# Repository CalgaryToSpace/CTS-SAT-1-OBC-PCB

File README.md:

# CTS-SAT-1-OBC-PCB

This is the design repository for the CTS-SAT-1 ("FrontierSat") onboard computer (OBC) PCB.

This OBC is host to an STM32 and several flash chips, and interfaces with all other electrical components on the 3U CubeSat.

## PCB Stackup

This PCB uses the [JLCPCB `JLC04161H-2116A` stackup](https://jlcpcb.com/impedance). It is a 6-layer, impedance-controlled PCB.

## Electrical Wire Comments

It is important to consider the outgassing characteristics of all wires used, so PTFE insulation has been chosen as the standard insulation material. The recommended part number is 5853 BK005, and the maximum recommended current is 1 amp per conductor.

If constructing Space Grade PCBs, use Rogers material as it has low outgassing properties.

## Repository Contents

* OBC PCB
* STM32CubeIDE Pinout/IOC configuration
* Unused early-stage umbilical connection board

## Contributors

* James Chen (contact chen.james2015@gmail.com with any questions)
* Others

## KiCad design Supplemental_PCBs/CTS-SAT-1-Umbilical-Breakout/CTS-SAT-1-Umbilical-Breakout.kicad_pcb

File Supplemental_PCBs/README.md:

# CTS-SAT-1 Supplemental PCBs

In this folder, two PCBs were used to support the development of the CTS-SAT-1 Onboard Computer (OBC).

* `Programming_Connector_Adapter_PCB`: Solder on to an Aliexpress ST-Link, and connect to the OBC with a 6-wide picoblade harness.
* `CTS-SAT-1-Umbilical-Breakout`: Works as a passthrough, and breaks out each pin for easy connection to USB-UART convert. Adds LEDs to each pin, as well as a polyfuse for safe charging.

## Subfolder Organization

* `./Programming_Connector_Adapter_PCB/` depends on `./lib/`.
* `./CTS-SAT-1-Umbilical-Breakout/` is self-contained.

## Render: `CTS-SAT-1-Umbilical-Breakout`

## Render: `Programming_Connector_Adapter_PCB`

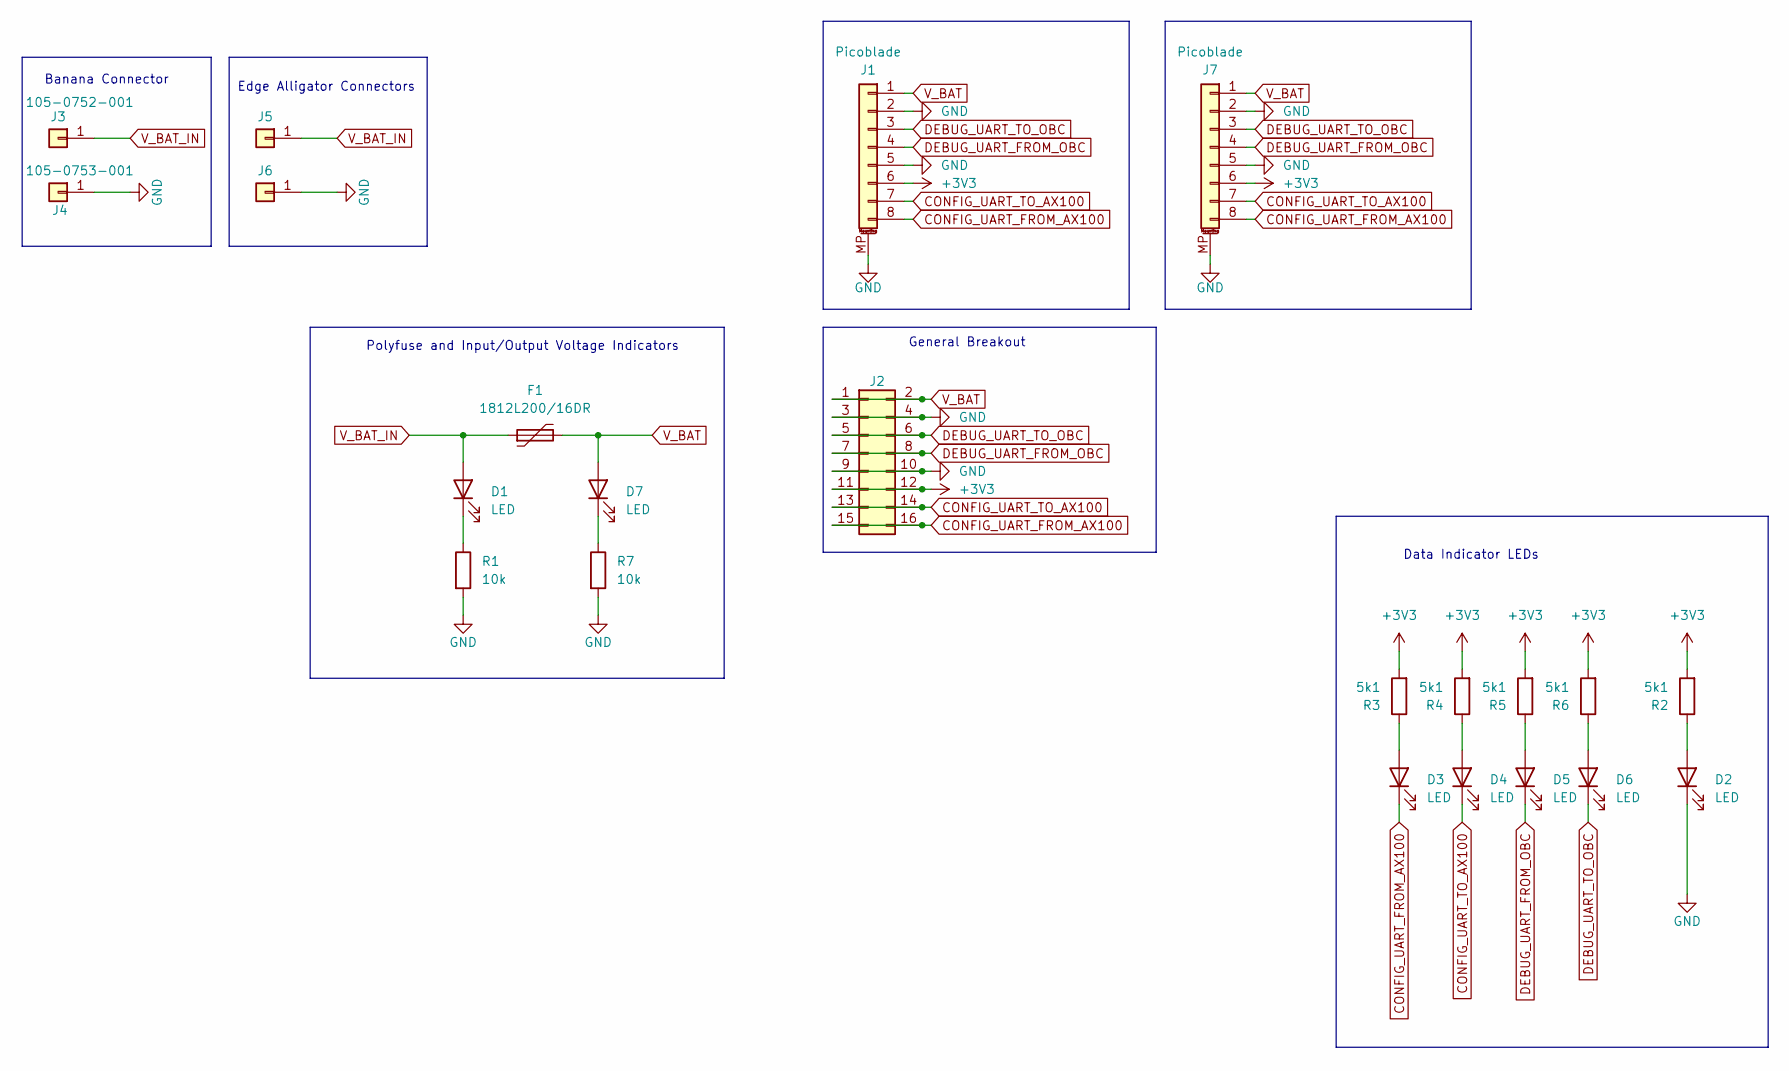
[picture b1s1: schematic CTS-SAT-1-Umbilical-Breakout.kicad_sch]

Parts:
D1, D2, D3, D4, D5, D6, D7: LED; LED_1206_3216Metric_Pad1.42x1.75mm_HandSolder
F1: 1812L200/16DR; Fuse_1812_4532Metric_Pad1.30x3.40mm_HandSolder
J1, J7: Picoblade; Molex_PicoBlade_53261-0871_1x08-1MP_P1.25mm_Horizontal
J2: Conn_02x08_Odd_Even; PinSocket_2x08_P2.54mm_Vertical
J3: 105-0752-001; TestPoint_Bridge_Pitch5.08mm_Drill1.3mm
J4: 105-0753-001; TestPoint_Bridge_Pitch5.08mm_Drill1.3mm
J5, J6: Conn_01x01; EdgeAlligatorConnector
R1, R7: 10k; R_1206_3216Metric_Pad1.30x1.75mm_HandSolder
R2, R3, R4, R5, R6: 5k1; R_1206_3216Metric_Pad1.30x1.75mm_HandSolder

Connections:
+3V3: J1.6, J2.11, J2.12, J7.6, R2.2, R3.2, R4.2, R5.2, R6.2
CONFIG_UART_FROM_AX100: D3.1 (K), J1.8, J2.15, J2.16, J7.8
CONFIG_UART_TO_AX100: D4.1 (K), J1.7, J2.13, J2.14, J7.7
DEBUG_UART_FROM_OBC: D5.1 (K), J1.4, J2.7, J2.8, J7.4
DEBUG_UART_TO_OBC: D6.1 (K), J1.3, J2.5, J2.6, J7.3
GND: D2.1 (K), J1.2, J1.5, J1.MP (MountPin), J2.3, J2.4, J2.9, J2.10, J4.1, J6.1, J7.2, J7.5, J7.MP (MountPin), R1.2, R7.2
unnamed: D1.1 (K), R1.1
unnamed: D2.2 (A), R2.1
unnamed: D3.2 (A), R3.1
unnamed: D4.2 (A), R4.1
unnamed: D5.2 (A), R5.1
unnamed: D6.2 (A), R6.1
unnamed: D7.1 (K), R7.1
V_BAT: D7.2 (A), F1.2, J1.1, J2.1, J2.2, J7.1
V_BAT_IN: D1.2 (A), F1.1, J3.1, J5.1

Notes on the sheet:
Banana Connector
Edge Alligator Connectors
Polyfuse and Input/Output Voltage Indicators
Data Indicator LEDs
General Breakout

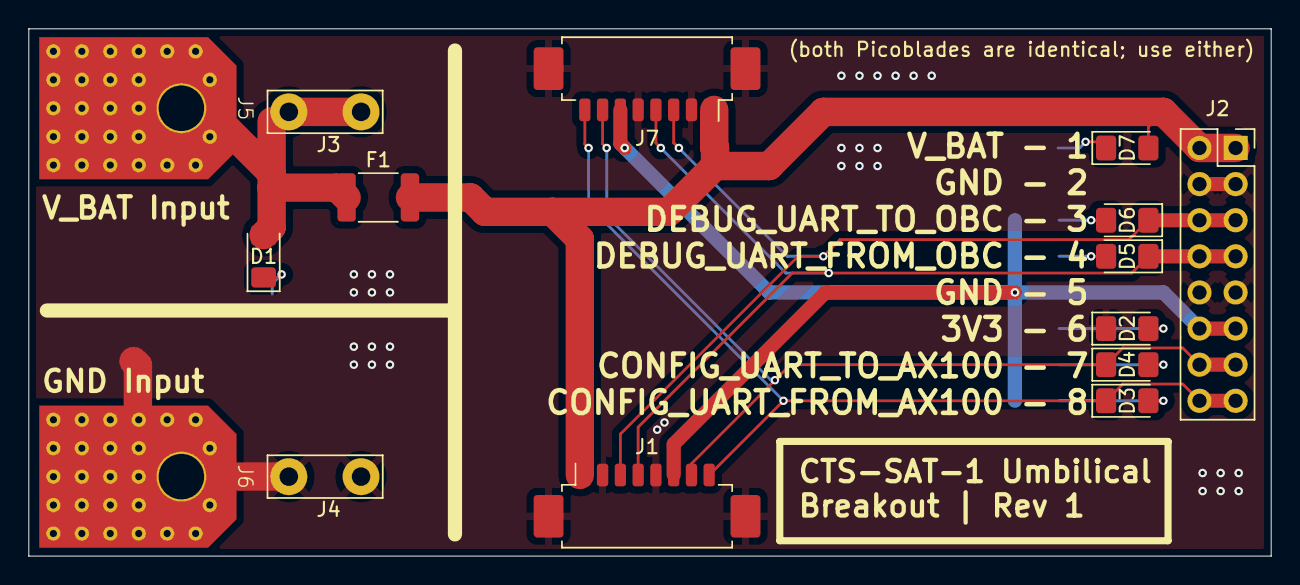
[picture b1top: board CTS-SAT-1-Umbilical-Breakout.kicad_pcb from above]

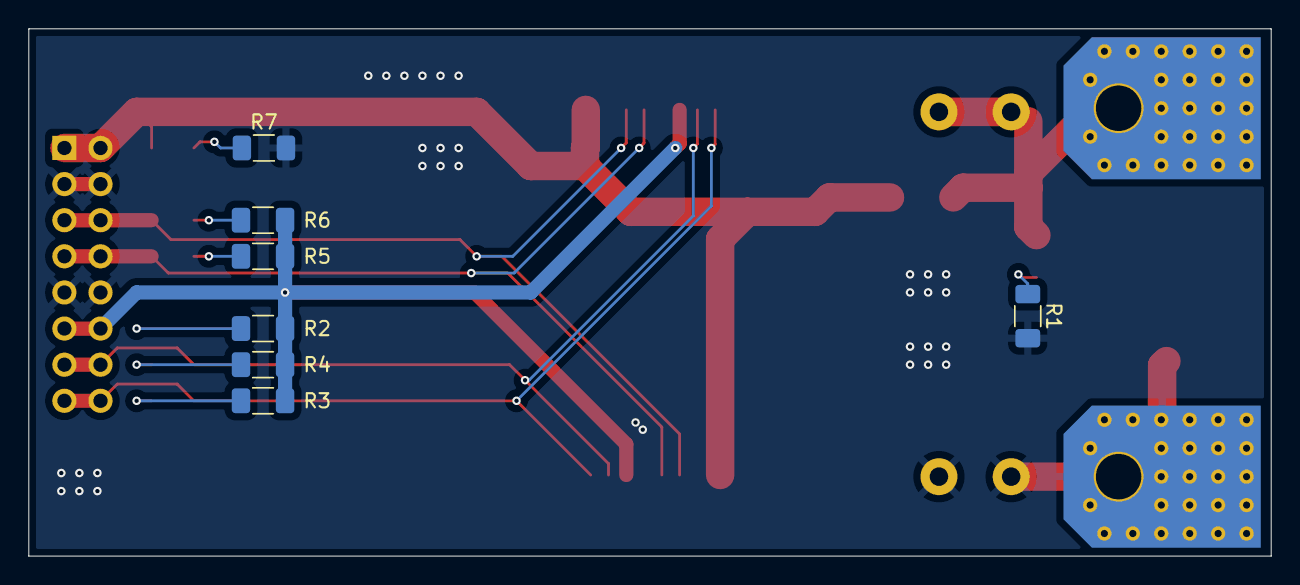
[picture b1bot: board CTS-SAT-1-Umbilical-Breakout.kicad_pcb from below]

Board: 2 copper layers, 87.4 x 37.1 mm, 22 parts (7 on the bottom side), 15 nets.

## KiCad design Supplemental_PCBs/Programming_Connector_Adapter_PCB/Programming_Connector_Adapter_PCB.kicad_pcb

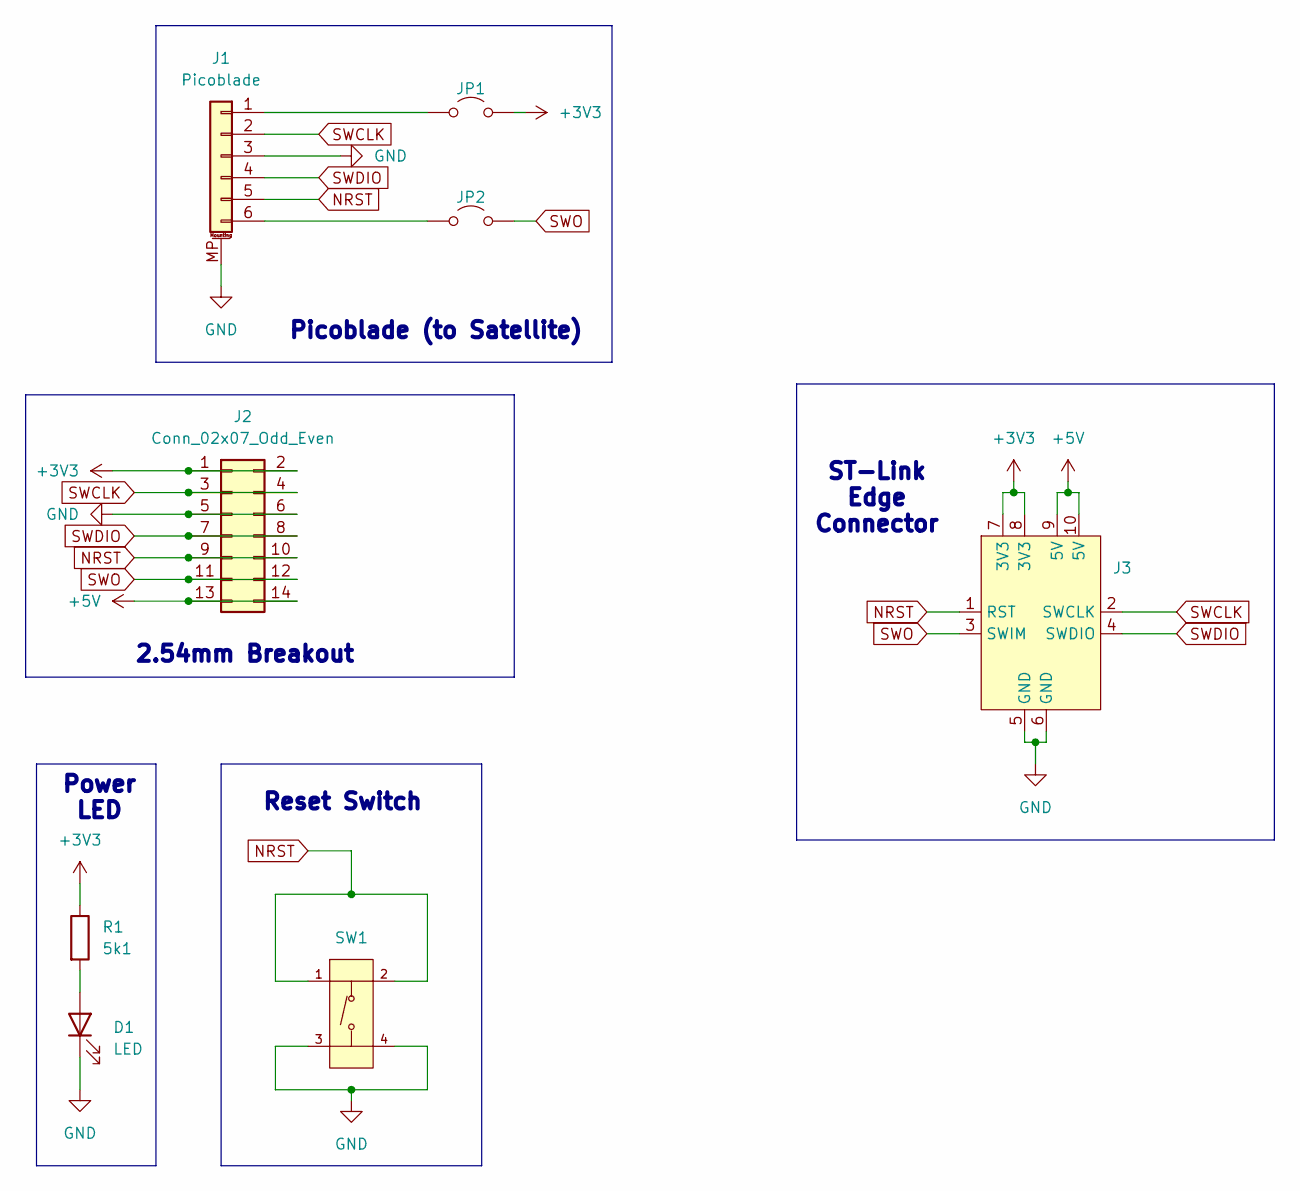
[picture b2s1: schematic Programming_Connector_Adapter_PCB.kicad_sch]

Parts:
D1: LED; LED_0603_1608Metric_Pad1.05x0.95mm_HandSolder
J1: Picoblade; Molex_PicoBlade_53261-0671_1x06-1MP_P1.25mm_Horizontal
J2: Conn_02x07_Odd_Even; PinHeaderSocket_2x07_P2.54mm_Vertical
J3: ST_Link_Edge_Connector
JP1, JP2: Jumper_2_Open; PinHeader_2x01_P2.54mm_Vertical
R1: 5k1; R_0603_1608Metric_Pad0.98x0.95mm_HandSolder
SW1: Tactile_Button,_160gf; SW-SMD_4P-L5.1-W5.1-P3.70-LS6.5-TL-2; Voltage Rating (Dc) 12V; Part TS-1187A-B-A-B; LCSC C318884

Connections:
+3V3: J2.1, J2.2, J3.7 (3V3), J3.8 (3V3), JP1.2 (B), R1.1
+5V: J2.13, J2.14, J3.9 (5V), J3.10 (5V)
GND: D1.1 (K), J1.3, J1.MP (MountPin), J2.5, J2.6, J3.5 (GND), J3.6 (GND), SW1.3 (C), SW1.4 (D)
NRST: J1.5, J2.9, J2.10, J3.1 (RST), SW1.1 (A), SW1.2 (B)
unnamed: D1.2 (A), R1.2
unnamed: J1.1, JP1.1 (A)
unnamed: J1.6, JP2.1 (A)
SWCLK: J1.2, J2.3, J2.4, J3.2 (SWCLK)
SWDIO: J1.4, J2.7, J2.8, J3.4 (SWDIO)
SWO: J2.11, J2.12, J3.3 (SWIM), JP2.2 (B)

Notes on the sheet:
2.54mm Breakout
Power LED
Reset Switch
ST-Link Edge Connector
Picoblade (to Satellite)

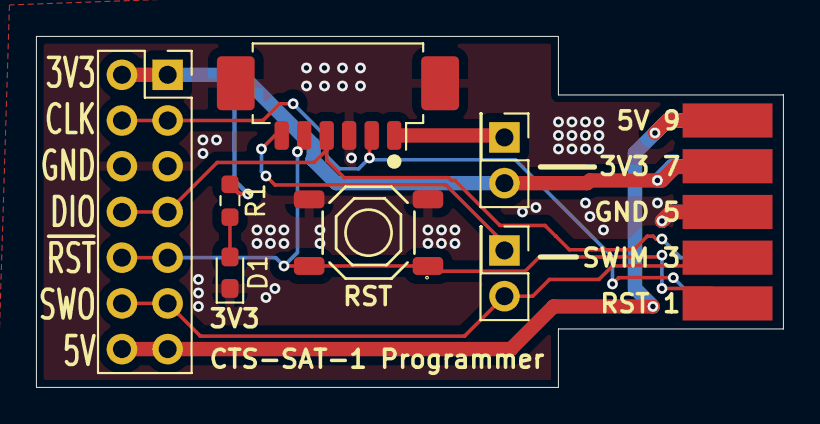
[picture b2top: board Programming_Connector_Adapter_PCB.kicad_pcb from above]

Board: 2 copper layers, 41.5 x 19.5 mm, 8 parts (0 on the bottom side), 10 nets.

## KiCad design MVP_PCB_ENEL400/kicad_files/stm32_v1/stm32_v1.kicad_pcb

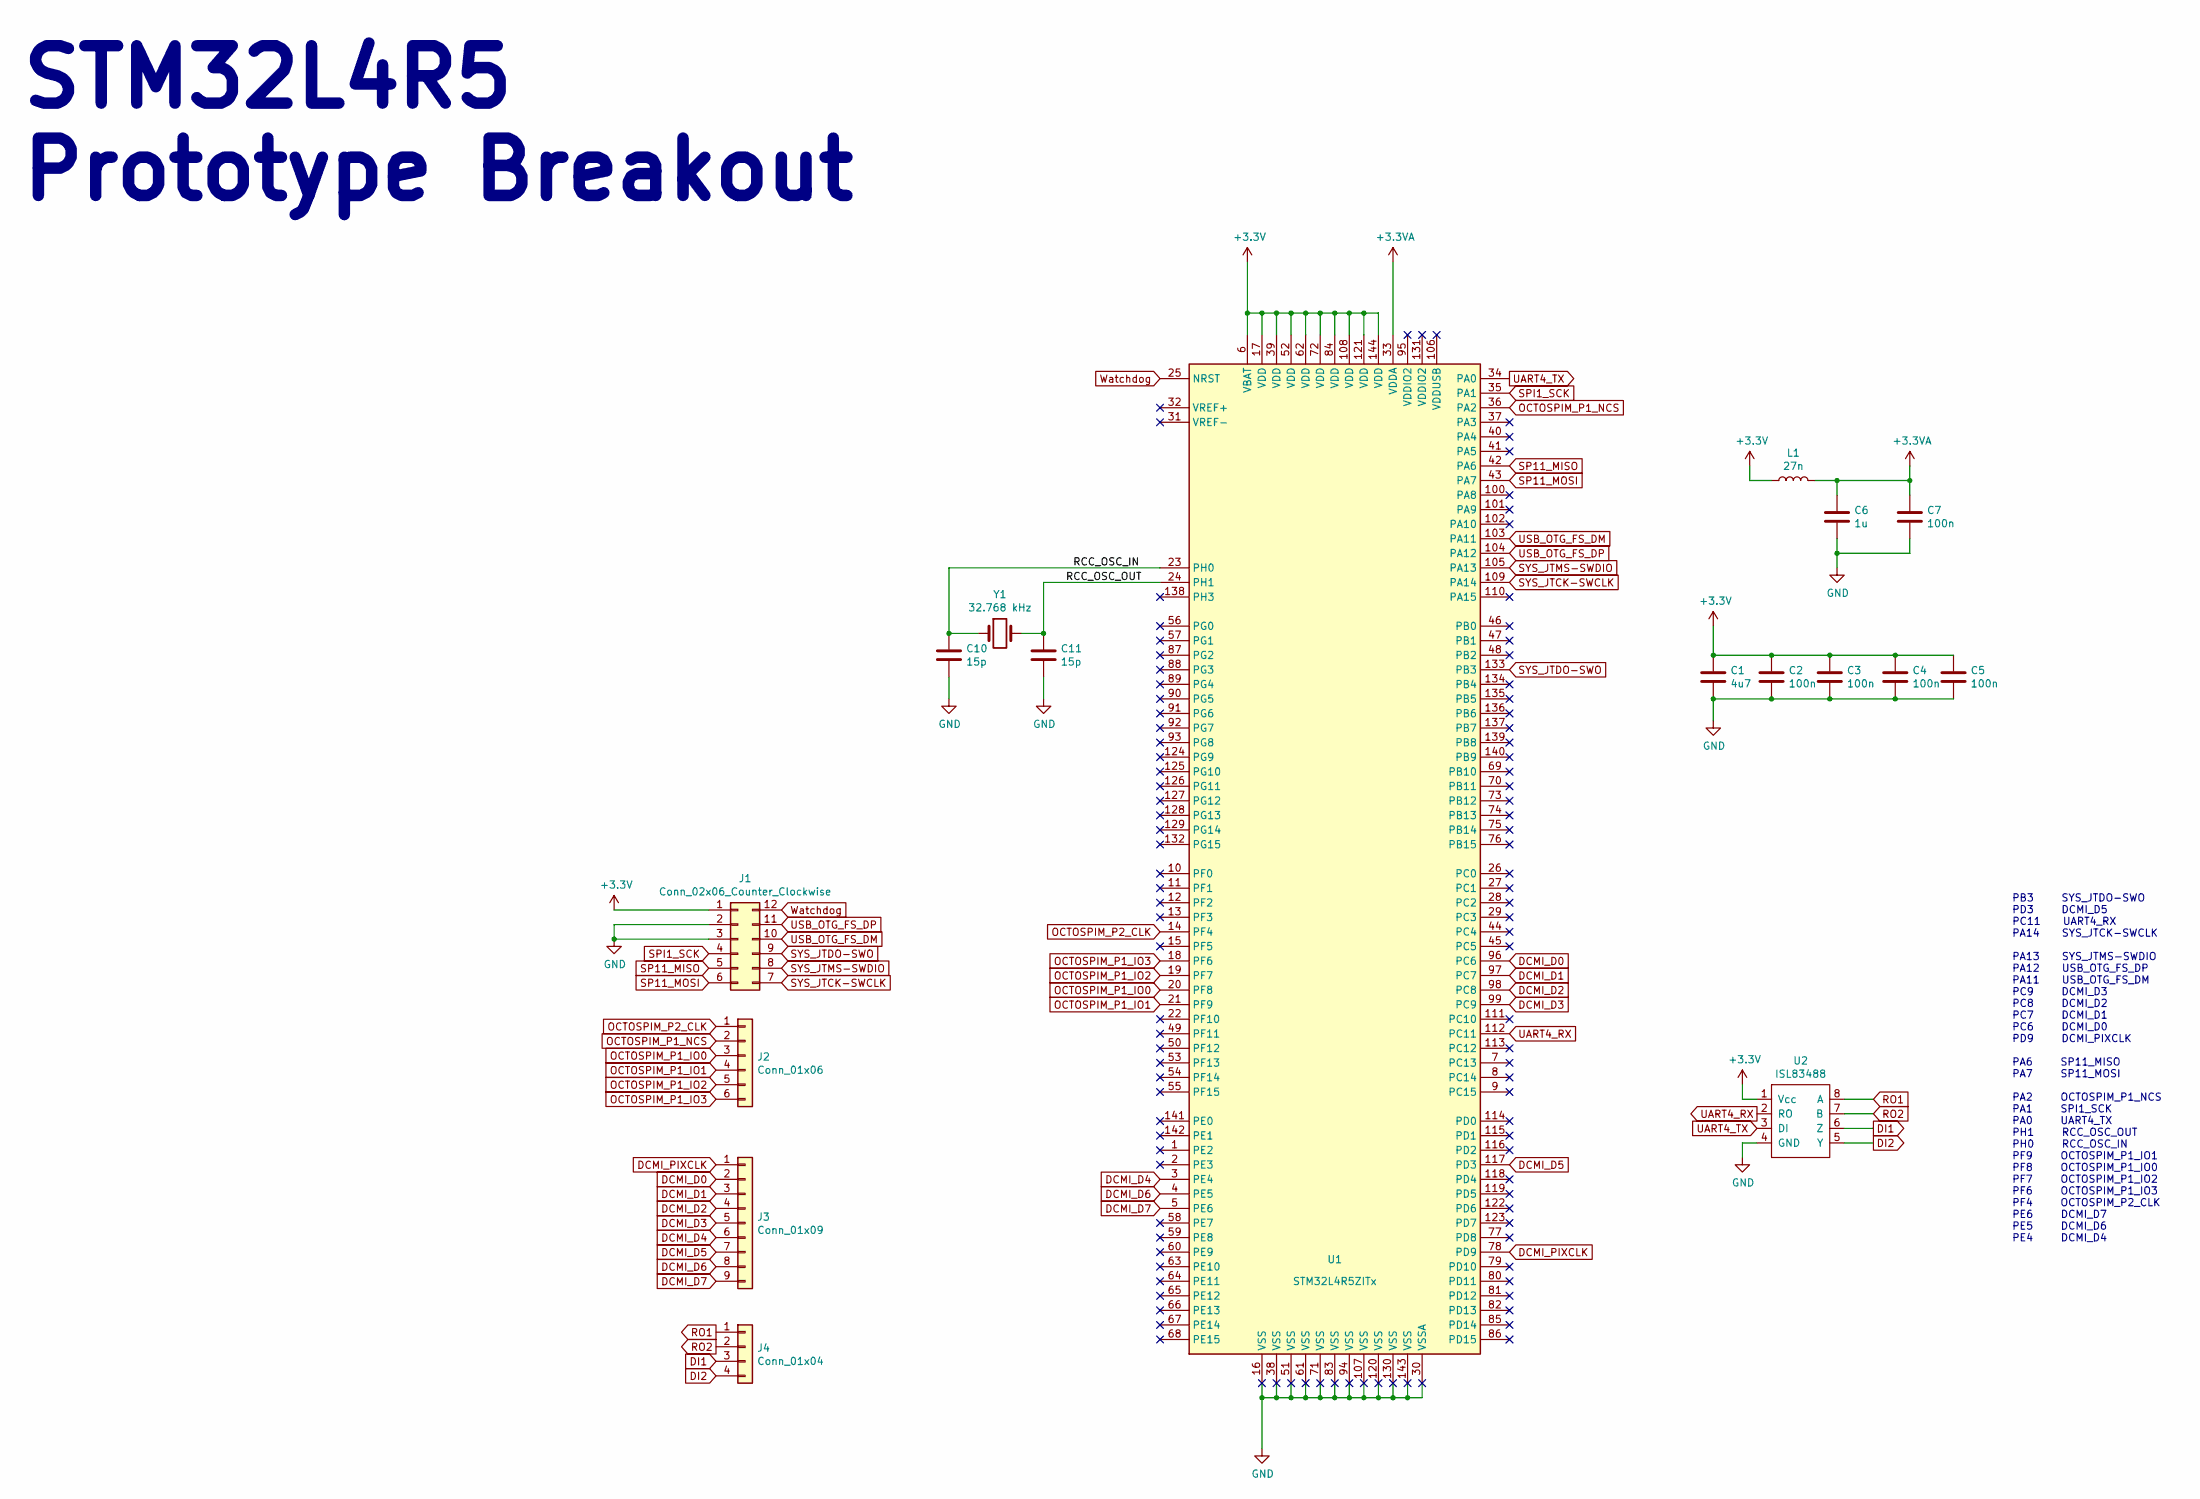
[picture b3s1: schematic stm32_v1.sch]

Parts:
C1: 4u7; C_0805_2012Metric_Pad1.18x1.45mm_HandSolder
C2, C3, C4, C5, C7: 100n; C_0805_2012Metric_Pad1.18x1.45mm_HandSolder
C6: 1u; C_0805_2012Metric_Pad1.18x1.45mm_HandSolder
C10, C11: 15p; C_0805_2012Metric_Pad1.18x1.45mm_HandSolder
J1: Conn_02x06_Counter_Clockwise; PinHeader_2x06_P2.54mm_Vertical
J2: Conn_01x06; PinHeader_1x06_P2.54mm_Vertical
J3: Conn_01x09; PinHeader_1x09_P2.54mm_Vertical
J4: Conn_01x04; PinHeader_1x04_P2.54mm_Vertical
L1: 27n; L_0805_2012Metric_Pad1.05x1.20mm_HandSolder
U1: STM32L4R5ZITx; LQFP-144_20x20mm_P0.5mm
U2: ISL83488; DIP-8_W8.89mm_SMDSocket_LongPads
Y1: 32.768 kHz; Crystal_SMD_2012-2Pin_2.0x1.2mm_HandSoldering

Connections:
+3.3VA: C6.1, C7.1, L1.2, U1.33 (VDDA)
+3V3: C1.1, C2.1, C3.1, C4.1, C5.1, J1.1, L1.1, U1.6 (VBAT), U1.17 (VDD), U1.39 (VDD), U1.52 (VDD), U1.62 (VDD), U1.72 (VDD), U1.84 (VDD), U1.108 (VDD), U1.121 (VDD), U1.144 (VDD), U2.1 (Vcc)
/RCC_OSC_IN: C10.1, U1.23 (PH0), Y1.1
/RCC_OSC_OUT: C11.1, U1.24 (PH1), Y1.2
DCMI_D0: J3.2, U1.96 (PC6)
DCMI_D1: J3.3, U1.97 (PC7)
DCMI_D2: J3.4, U1.98 (PC8)
DCMI_D3: J3.5, U1.99 (PC9)
DCMI_D4: J3.6, U1.3 (PE4)
DCMI_D5: J3.7, U1.117 (PD3)
DCMI_D6: J3.8, U1.4 (PE5)
DCMI_D7: J3.9, U1.5 (PE6)
DCMI_PIXCLK: J3.1, U1.78 (PD9)
DI1: J4.3, U2.6 (Z)
DI2: J4.4, U2.5 (Y)
GND: C1.2, C2.2, C3.2, C4.2, C5.2, C6.2, C7.2, C10.2, C11.2, J1.2, J1.3, U1.16 (VSS), U1.30 (VSSA), U1.38 (VSS), U1.51 (VSS), U1.61 (VSS), U1.71 (VSS), U1.83 (VSS), U1.94 (VSS), U1.107 (VSS), U1.120 (VSS), U1.130 (VSS), U1.143 (VSS), U2.4 (GND)
OCTOSPIM_P1_IO0: J2.3, U1.20 (PF8)
OCTOSPIM_P1_IO1: J2.4, U1.21 (PF9)
OCTOSPIM_P1_IO2: J2.5, U1.19 (PF7)
OCTOSPIM_P1_IO3: J2.6, U1.18 (PF6)
OCTOSPIM_P1_NCS: J2.2, U1.36 (PA2)
OCTOSPIM_P2_CLK: J2.1, U1.14 (PF4)
RO1: J4.1, U2.8 (A)
RO2: J4.2, U2.7 (B)
SP11_MISO: J1.5, U1.42 (PA6)
SP11_MOSI: J1.6, U1.43 (PA7)
SPI1_SCK: J1.4, U1.35 (PA1)
SYS_JTCK-SWCLK: J1.7, U1.109 (PA14)
SYS_JTDO-SWO: J1.9, U1.133 (PB3)
SYS_JTMS-SWDIO: J1.8, U1.105 (PA13)
UART4_RX: U1.112 (PC11), U2.2 (RO)
UART4_TX: U1.34 (PA0), U2.3 (DI)
USB_OTG_FS_DM: J1.10, U1.103 (PA11)
USB_OTG_FS_DP: J1.11, U1.104 (PA12)
Watchdog: J1.12, U1.25 (NRST)

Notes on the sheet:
PB3 SYS_JTDO-SWO PD3 DCMI_D5 PC11 UART4_RX PA14 SYS_JTCK-SWCLK PA13 SYS_JTMS-SWDIO PA12 USB_OTG_FS_DP PA11 USB_OTG_FS_DM PC9 DCMI_D3 PC8 DCMI_D2 PC7 DCMI_D1 PC6 DCMI_D0 PD9 DCMI_PIXCLK PA6 SP11_MISO PA7 SP11_MOSI PA2 OCTOSPIM_P1_NCS PA1 SPI1_SCK PA0 UART4_TX PH1 RCC_OSC_OUT PH0 RCC_OSC_IN PF9 OCTOS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
STM32L4R5 Prototype Breakout

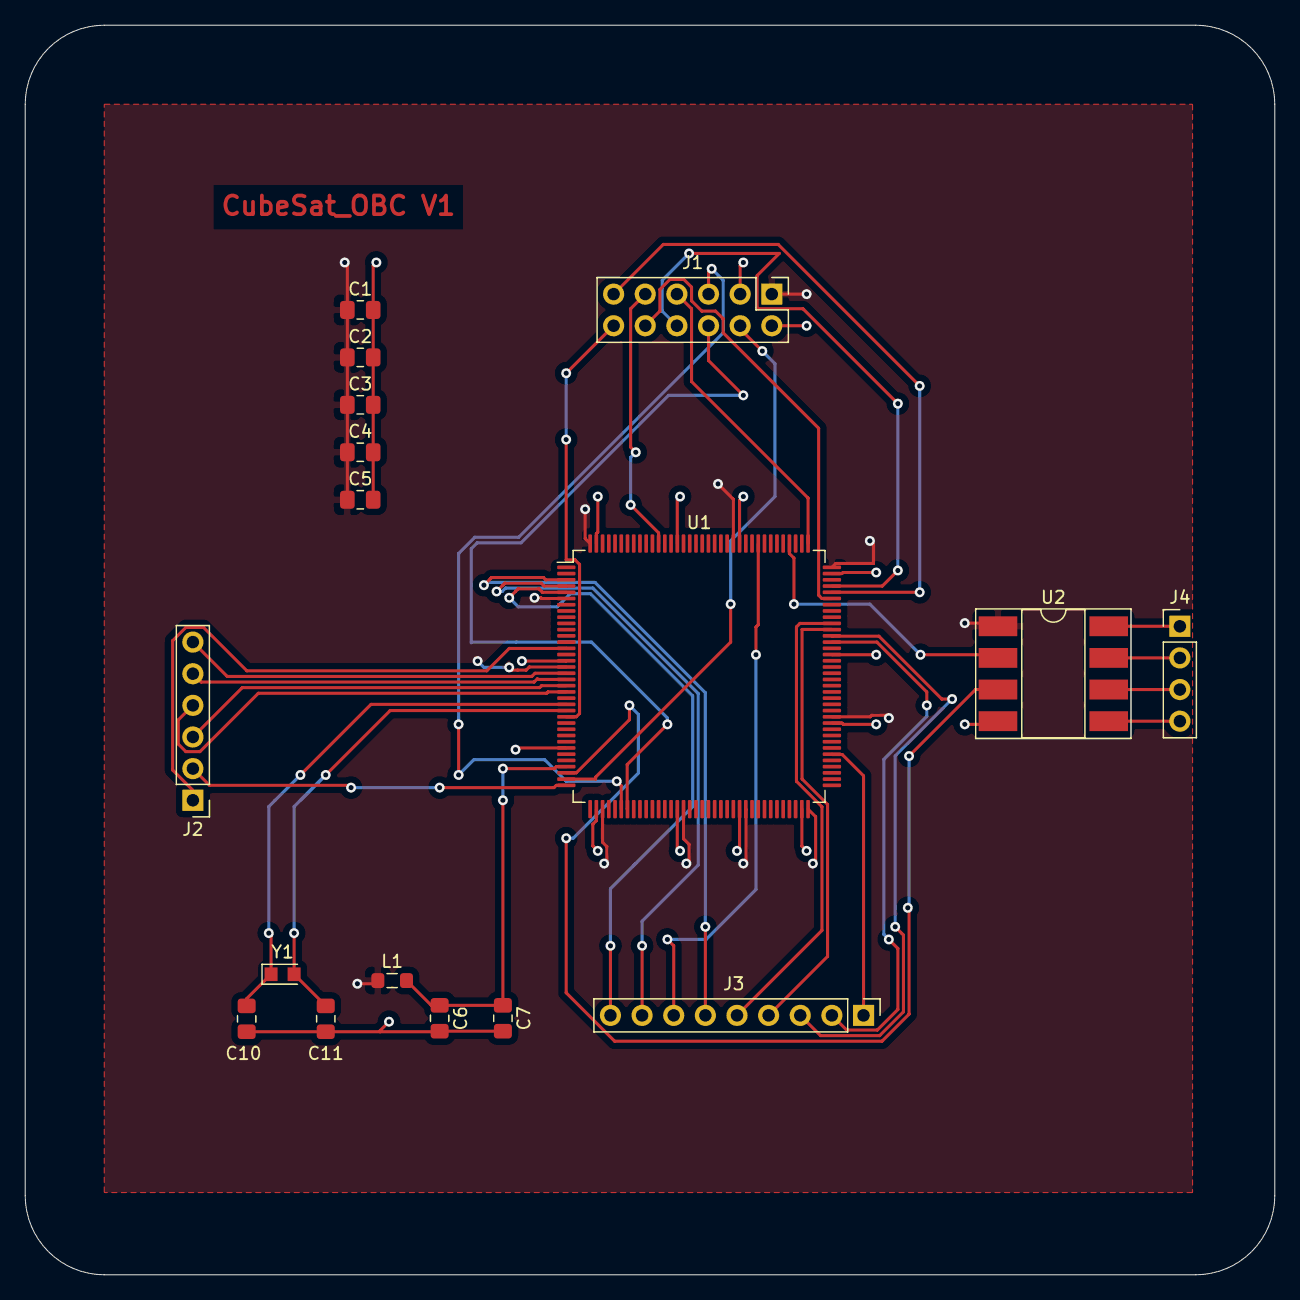
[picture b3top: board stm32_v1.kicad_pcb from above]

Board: 2 copper layers, 100.3 x 100.3 mm, 17 parts (0 on the bottom side), 35 nets.

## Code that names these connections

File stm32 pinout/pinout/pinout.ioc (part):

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PG8.Mode=I2C
PB13.GPIOParameters=GPIO_Label
Mcu.UserName=STM32L4R5ZITxP
PD9.GPIOParameters=GPIO_Label
PH0-OSC_IN\ (PH0).Signal=RCC_OSC_IN
PG4.Signal=GPIO_Output
PG8.Signal=I2C3_SDA
PB14.GPIO_Label=MOTOR_PWM
PG0.Signal=GPIO_Output
PA6.GPIO_Label=GPS_PPS
PC5.Mode=Asynchronous
PB13.GPIO_Label=MOTOR_NEN
PG5.GPIO_Label=MPI_TX_EN
PB13.Signal=GPIO_Output
PB15.Signal=GPIO_Output
PG13.Signal=I2C1_SDA
PA2.GPIOParameters=GPIO_Label
RCC.SYSCLKSource=RCC_SYSCLKSOURCE_HSE
PA14\ (JTCK/SWCLK).Signal=SYS_JTCK-SWCLK
PE4.GPIOParameters=GPIO_Label
PD11.GPIO_Label=ENCODER_A
PD8.GPIOParameters=GPIO_Label
PD8.Signal=GPIO_Output
PD5.Mode=Asynchronous
PD10.GPIOParameters=GPIO_Label
RCC.HSE_VALUE=25000000
PB12.GPIO_Label=MOTOR_NFAULT
PG14.Mode=I2C
PG1.GPIOParameters=GPIO_Label
PE13.Signal=SPI1_SCK
PE9.Signal=GPIO_Output
PG4.GPIO_Label=MPI_RX_NEN
PA0.Mode=Asynchronous
PE4.GPIO_Label=GPLED3
PE3.GPIOParameters=GPIO_Label
PE2.Signal=GPIO_Output
PA14\ (JTCK/SWCLK).Mode=Trace_Asynchronous_SW
PE13.Mode=Full_Duplex_Master
PG13.Mode=I2C
PE4.Signal=GPIO_Output
PA0.Signal=UART4_TX
Mcu.Package=LQFP144
PA6.Signal=GPIO_Input
PG5.GPIOParameters=GPIO_Label
PA2.GPIO_Label=CAMERA_EN
PA10.Signal=USART1_RX
PG0.GPIO_Label=FLASH_NCS_A2
PB14.GPIOParameters=GPIO_Label
PF0.Signal=I2C2_SDA
PC5.Signal=USART3_RX
PE7.Signal=GPIO_Output
PH0-OSC_IN\ (PH0).Mode=HSE-External-Clock-Source
PE2.GPIO_Label=GPLED1
PC4.Mode=Asynchronous
PA3.Signal=USART2_RX
PA6.GPIOParameters=GPIO_Label
PE8.GPIOParameters=GPIO_Label
PG7.Signal=I2C3_SCL
PA13\ (JTMS/SWDIO).Mode=Trace_Asynchronous_SW
PD9.GPIO_Label=ENCODER_I
PA10.Mode=Asynchronous
PG1.Signal=GPIO_Output
PG5.Signal=GPIO_Output
PC4.Signal=USART3_TX
PD9.Signal=GPIO_Output
PD5.Signal=USART2_TX
PE9.GPIOParameters=GPIO_Label
PD8.GPIO_Label=ENCODER_EN
PD10.Signal=GPIO_Output
PA3.Mode=Asynchronous
PF1.Mode=I2C
PA9.Mode=Asynchronous
PB3\ (JTDO/TRACESWO).Signal=SYS_JTDO-SWO
PE7.GPIOParameters=GPIO_Label
PE8.GPIO_Label=FRAM_NCS_1
PA9.Signal=USART1_TX
PE2.GPIOParameters=GPIO_Label
PD10.GPIO_Label=ENCODER_B
PG7.Mode=I2C
PE9.GPIO_Label=FRAM_NCS_0
PA1.Signal=UART4_RX
PB14.Signal=S_TIM15_CH1
PG14.Signal=I2C1_SCL
board=custom
PG1.GPIO_Label=FLASH_NCS_A1
PD11.GPIOParameters=GPIO_Label
PA1.Mode=Asynchronous
PE14.Signal=SPI1_MISO
PE15.Signal=SPI1_MOSI
PG4.GPIOParameters=GPIO_Label
PB15.GPIO_Label=MOTOR_DIR
PE8.Signal=GPIO_Output
PE14.Mode=Full_Duplex_Master
PF1.Signal=I2C2_SCL
PB15.GPIOParameters=GPIO_Label
Mcu.Name=STM32L4R5ZITxP
PE7.GPIO_Label=FLASH_CS_A0
PA2.Signal=GPIO_Output
RCC.SYSCLKFreq_VALUE=25000000
PD11.Signal=GPIO_Output
PF0.Mode=I2C
PG0.GPIOParameters=GPIO_Label
PB3\ (JTDO/TRACESWO).Mode=Trace_Asynchronous_SW
PE3.Signal=GPIO_Output
PE3.GPIO_Label=GPLED2
PB12.GPIOParameters=GPIO_Label
PB12.Signal=GPIO_Output
PA13\ (JTMS/SWDIO).Signal=SYS_JTMS-SWDIO
PE15.Mode=Full_Duplex_Master

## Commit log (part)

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2021-02-06 testing
2021-02-06 added setup files for obc design
2021-06-09 Changed to Altium, added inital work
2021-06-27 Schematic change, QSPI to SPI, chnage TCXO to XO
2021-08-08 added PC104 header labels, added load caps for oscillator
2021-08-20 added GPS connector, series resistors and pull ups to STM
2021-10-02 added 3rd flash chip
2021-10-08 remove archive, change directory structure
2021-10-18 Added RS422 circuit, STM pinout
2021-10-30 add LDO, swap STM32 for 144pin
2021-11-02 update git ignore
2021-11-13 update STM32
2021-11-22 Motor controller, encoder circuitry added, current draw comments
2021-12-15 add camera pinout
2021-12-18 Setup variant, remove ext clk from camera
2021-12-18 changed to 2mm pitch, need to check if correct
2021-12-19 Revert "debug"
    This reverts commit a9be2125b960059e23b02acd5c2186153c76f217.
2021-12-19 remove redundant stm32 resistors, initial component placement
2021-12-20 Add voltage translator, change mounting holes to pads
2021-12-26 additional power routing
2021-12-28 Camera Routing and misc
2021-12-28 memory routing
2022-01-07 rearrange controlled impedance traces, resolve design rule errors
2022-01-08 Branch separation
2022-01-08 Add logo, labels to silk screen
2022-01-14 Schematic for 5V Buck
2022-01-28 added new schematic
2022-02-04 push
2022-02-04 adding_descriptions
2022-02-17 add descriptions and part numbers
2022-03-07 update schematic
2022-03-07 corrected switch errors
2022-03-12 restructure file directory
2022-03-19 begin rev1.1 of obc, remove unnecessary components
2022-03-19 connector and mounting hole updates
2022-03-25 minor changes
2022-03-26 add umbilical connector
2022-04-17 connector changes
2022-04-23 completed majority of routing
2022-05-06 updated uart connections
2022-05-11 update FRAM footprint
2022-05-11 remove old documents
2022-05-18 minor changes and cleanup from design review
2022-05-20 generate fabrication outputs
2022-06-17 Add obc rev 1.1 pinout .ioc file, stm32cubeIDEproject
2023-03-09 commit burn wire development board
2023-04-12 outline of changes to come in rev 1.2
2023-04-18 update schematic library
2023-05-01 rough component and connector layout
    layout most connector locations subject to change. and placed sensitive components
2023-05-08 resolve errors and generate design files
2023-05-10 change debug uart pinout
    swap tx/rx on stm and umbilical
2023-05-10 update output job file
2023-08-30 Version3: Update pad placements for Y-TG2520SMN 20.0000M-MCGNNM3 (need to re-layout)
2023-08-30 Version3: Change R107 and R109 to 0 ohm resistors to stop distortion
2023-08-30 Remove gitignored files
2023-08-30 Version3: Update ReadMe
2023-08-30 Version3: Update ReadMe and pin designations
2023-09-16 Version3: Remove R68
2023-09-16 Version3: Update footprint for ECS-TXO clock
2023-09-16 Version3: Fix footprint silkscreens
2023-09-16 Version3: As done as it can be without burnwire and rf switch testing
2023-09-23 Migrate IOC file
2023-09-23 Version3: Break RX, TX, ground for umbilical into 2.5 headers
2023-09-23 Version3: Verify EPS
2023-09-26 Version3: Update reqs
2023-10-06 Add MPI UART transmit testing (MOSI test)
2023-10-07 Version3: Finish schematic changes
2023-10-25 Version3: Schematic ready for review
2023-11-04 Version3: Update net labels
2023-11-07 Write transceiver state setter, test working
2023-11-15 Version3: Relabel RX/TX on U1A
2023-12-15 Version3: PR Comments
2023-12-15 Version3: Finish messing with schematic
2023-12-15 Version3: Update chips
2023-12-20 Version3: Update BOM
2023-12-22 Version3: Update burnwire config
2024-01-20 Version3: Working on components
2024-02-24 Version3: Finish routing
2024-02-28 Version3: Update outjobs
2024-02-28 Version3: Finish schematic
2024-03-23 swapped debug UART and antenna B I2C
    Schematic: swap debug LPUART1 and I2C_3. Now:
    - PC0 = Ant B SCL (I2C_3)
    - PC1 = Ant B SDA (I2C_3)
    - PG8 = Debug UART MISO RX (LPUART1)
    - PG7 = Debug UART MOSI TX (LPUART1)
2024-03-23 R70/R71 rerouting
    - Moved in R70 and R71 (routed these to the respective 3V3/GND vias and I2C connections on the microcontroller)
    - Moved C10 over (not 100% sure but might've moved C14 as well in the process - very minor change regardless) to make room
    - Rotated resistors around to make room / adjusted global text size
    Todo:
    - Finish routing I2C connections from R70/R71 to back to the top near (U15)
2024-04-03 made routing changes
    put resistor into place, and re-routed Nreset
2024-04-06 Cleared some DRC errors
    Updates footprint slikscreen for J-53261-0471 and cleared room(s) at bottom left of layout
2024-04-06 Cleared all Silk screen errors
2024-04-06 Ran DRC
2024-04-06 I2C routing
    finished routing I2C_4 (I2C_SDA and I2C_SCL)
2024-04-27 added labelling for H1 & H2
    - added lines to indicate every 10 pins for H1 & H2 for top overlay
    -added rectangle and numbers to indicate pins for H1 & H2 for bottom overlay
    -Ran DRC & repour (no changes made)
2024-04-27 Resolved DRC regarding clearance
    - changed the pin 1 indicator that were causing the clearance error.
    -changed thickness of the differential pair routing from 10 mil to 5.8 mil. Now the only error left is the length of the differential pair
    - Dead solder DRC error, can be ignored and agreed by Parker
2024-06-15 Edited Schematics
    Removed EU LoRa and used freed UART5 line for EPS. Created switch for UART2 lines connecting it to both the PC104 and the US LoRa.
2024-06-18 Extra save
2024-06-22 Cleared DRC Silkscreen Errors
    Silkscreen errors on R72 and R73 cleared. Note* that previous mentions of rerouting burnwire and boom deployment circuitry were scrapped after further research.
2024-06-29 Created .Step file for latest version
    Please merge to main branch
2024-07-03 Used latest OBC review to fix design errors
    Ensured stitching vias did not encroach into keep-out zones. Rerouted COMS to clear some space near RF portion of layout. Fixed name changes on schematic and title blocks.
2024-07-06 Cleared polygon shards
2024-07-11 Placed new 47uF capacitors for boom deployment circuit, added Burn Wire Dev Board Library to project
2024-07-12 Reorganized burnwire circuitry
    Replaced components for boom control circuitry, with emphasis placed on high current movement. U4, L1, R62, J8 and J9 identified as high current loop, and thus were placed in close proximity. Routing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
2024-07-12 Switched 22/0 ohm resistors, added 0.1uF capacitor to NBOOT or Clock, Added footprints for ceramic capacitors for burnwire circuit
2024-07-12 Changed C34 on burnwire circuit
2024-07-12 Updated layout
2024-07-13 Adjusted thermal reliefs
    Adjusted thermal reliefs on burnwire circuitry to account for high current flow.
2024-07-15 Replaced R33 with 0.33Ohm 4W resistor, added part to OBC Schematic Library
2024-07-16 Added MT29F16G08ABACAWP-AAT:C TR memory module, made its schematic, footprint, and step file, started creating pin/wire connections based on details from the datasheet
2024-07-18 Added some wiring to the new flash module
2024-07-18 Made SPI_NCS_FLASH_6 and SPI_NCS_FLASH_7 on the STM32 Schematic "No Connection" (they are not needed for the new flash module replacements)
2024-07-19 Finished routing new memory modules.
    Note that some small silkscreen changes need to be made.
2024-07-20 Rearranged vias around 3V3 LoRa trace to increase surrounding copper coverage
2024-07-22 Further updated driver-side series resistor placement.
2024-07-22 Updated J14 Label
2024-07-23 Connected series resistors to driver side MISO pins
    Added 22 ohm resistors (6 total) to each flash and fram module along the MISO lines and routed them.
2024-07-27 Added a backup "remove before flight" connector
    Added picoblade connects along with 8 resistors to create a remove-before-flight connector. Two random GPIO pins were chosen on the STM, and were hooked up to the connecter. The connector was then al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
2024-08-02 Updated Schematic PDFs
2024-08-06 Added 22ohm terminating resistor to LOA_MOSI_UART2_TX, added 0ohm terminating resistor to LORA_MISO_UART2_RX
2024-08-07 Added series resistors to RX and TX lines on the MPI
2024-08-07 Added new 25V rated tantalum capacitor to boom deployment circuit
2024-08-08 Routed driver side resistors for MPI and LoRa signal comms lines
2024-08-10 Rearranged pinout of MPI Power In connector
    The "MPI Power In" connector mates with J7 on the EPS - in order to make the connection easier to facilitate, the pinout of the MPI connector was rearranged to mirror the pinout of J7 (noting that I2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
2024-08-10 Add current JLCPCB PCB layer stackup to README
2024-08-12 Generated new outjob files
2024-08-17 Used the PCB Filter tool to resize trace widths
    In order to maintain the 50ohm impedence on all layers, all* external signal traces were changed from 10mil to 7.33mils and internal traces changed to 7.04mils. Exceptions were made to any traces rel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
2024-08-17 Cleaned up repository
2024-08-17 Extra save for release
2024-08-17 Created new outjob for Schematic PDF
2024-08-21 Updated OBC Outjob
2024-08-21 Remade output files, ensuring to include drill files in fab package
2025-01-08 Naming convention changes
    Changed the naming convention used in the schematic for the Programming/SWD connectors
2025-01-11 Modified RBF connector
    Removed RBF2, resulting in the elimination of R78, R80 and R82. Also results in PB15 becoming a NC. Note that further modifications to the RBF connector are also needed.
2025-01-14 Updated connectors on schematic and layout
    Changed J15 from a 4-pin connector to a 2-pin connector connected to RBF1 and GND. Resulted in the removal of R68. Updated layout after removal of J21 on the schematic.
2025-01-15 Extra save
    Extra save
2025-01-18 Updated Reset line on SWD connector
    Replaced 0R with 22R on reset line coming from the SWD picoblade connector in order to eliminate previously occurring contention problem.
2025-01-18 Shifted Reset switch
    Shifted Reset switch
2025-01-23 Updated layout of Crystals
    Rearranged Y2 and Y1 on layout
2025-01-29 Fixed the NRST contention
    Added series resistor to RST button to fix contention issues.
2025-02-01 Moved MPI transceiver to the front of the board
    Need to still route diff pairs.
2025-02-06 Rerouting memory IC passives
2025-02-06 Moved R83 and R84 to the frontside
2025-02-14 added .step file export
2025-02-18 Deleted Boom Control Schematic Sheet
2025-03-01 Routed Spare UART connector
    Routed spare UART connector (J9) - replaced series resistor on all LEDs with 4.7k ohm resistors (originally 220 ohms)
2025-03-01 Created New OutJob
2025-03-03 Rounded board corners
2025-03-05 Added 100k resistor to schematic library and used them to pull down floating metal on inverter (U14) and Camera connector
2025-03-08 Added pull down resistors to all floating pins
    Added 100k pull down resistors to any pins left floating on the GPS, Camera, MPI and Antenna connectors.
2025-03-08 Added 10k pull up resistors to WP on all flash modules
    Added 10k pull ups to WP pins on all flash modules to prevent floating metal. WP pins are active low
2025-03-12 Laid out pull down resistors on PC104 stack
    Still need to route
2025-03-13 Created Outjob for OBC
2025-03-15 Updated Outjob
    Updated fab/assembly files to 7PCB standards and requirements.
2025-03-19 Updated stack header footprint
    Updated stack header footprint with correct pin designators and added it to the schametic/layout.
2025-03-19 Generated new output job
2025-05-27 Schematic update
    Changed BOOM CTRL pin labels on schematic to reflect updated functionality
